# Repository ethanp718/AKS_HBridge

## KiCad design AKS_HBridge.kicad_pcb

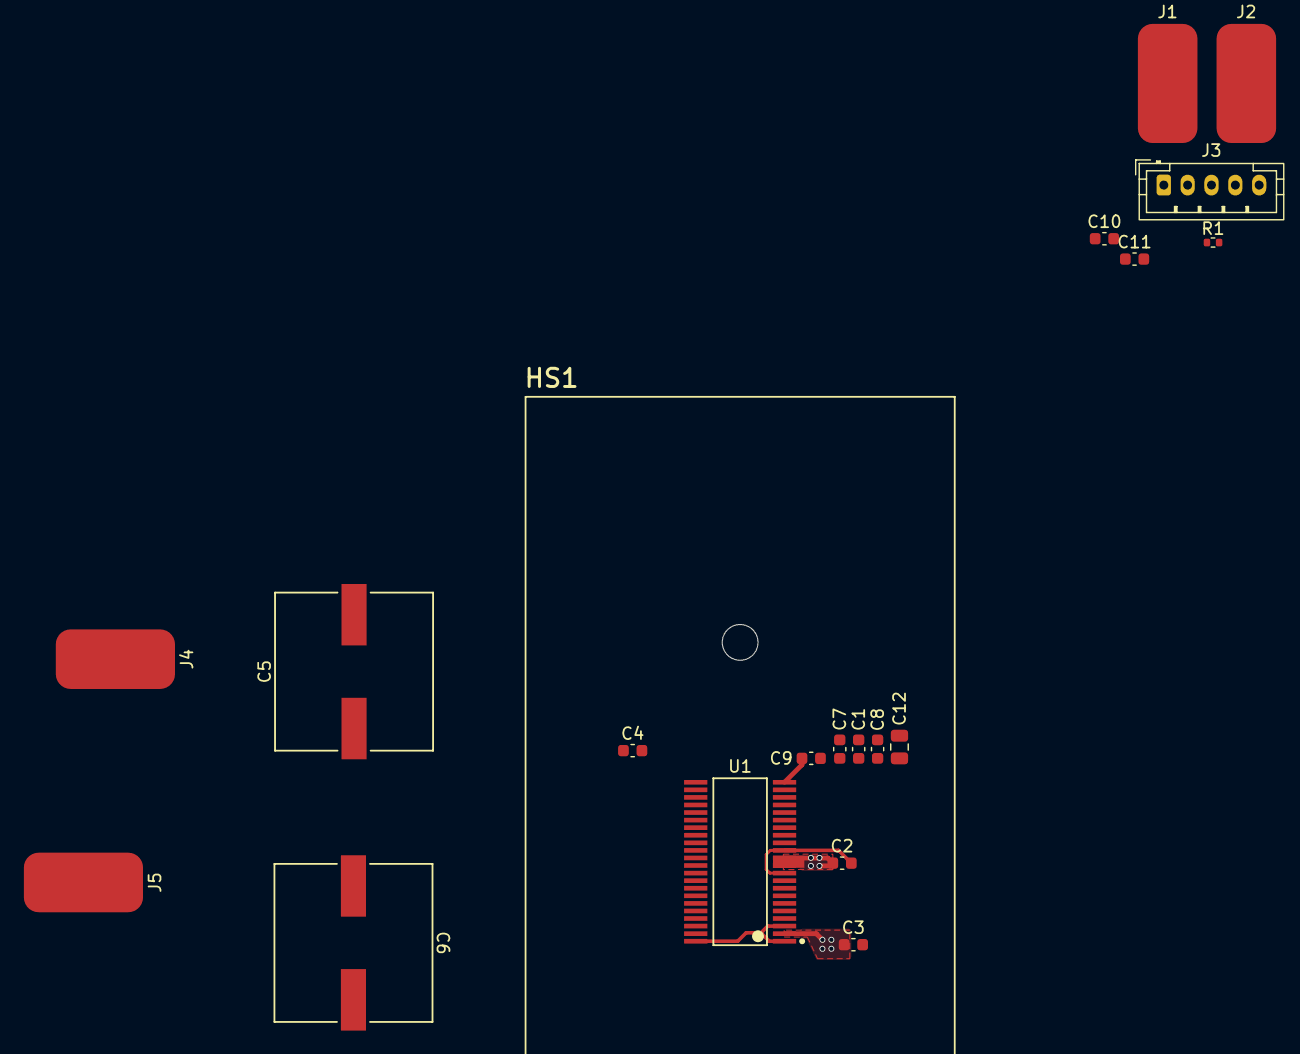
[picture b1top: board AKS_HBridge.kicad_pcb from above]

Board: 4 copper layers, 20 parts (0 on the bottom side), 12 nets.

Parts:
C1, C2, C3: 10nF; C_0603_1608Metric
C4, C8, C11: 100nF; C_0603_1608Metric
C5, C6: 100uF; CHEMI-KE0
C7: 1nF; C_0603_1608Metric
C9, C10: 1uF; C_0603_1608Metric
C12: 1uF; C_0805_2012Metric
HS1: Heatsink_Pad; FP-ATS-TI10P-519-C1-R3_HEAT_SINK-MFG
J1: MOTA; SolderWirePad_1x01_SMD_5x10mm
J2: MOTB; SolderWirePad_1x01_SMD_5x10mm
J3: Control; JST_PH_B5B-PH-K_1x05_P2.00mm_Vertical
J4: BATT+; SolderWirePad_1x01_SMD_5x10mm
J5: BATT-; SolderWirePad_1x01_SMD_5x10mm
R1: 10k; R_0402_1005Metric
U1: DRV8262DDVR; DDV0044E-IPC_A

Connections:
/FAULT_N: J3.4, R1.2, U1.41 (FAULT_N)
/IN1: J3.1, U1.26 (IN1)
/IN2: J3.2, U1.27 (IN2)
/MOTA: J1.1 (Pin_1_1), U1.4 (OUT3), U1.5 (OUT3), U1.6 (OUT3), U1.17 (OUT1), U1.18 (OUT1), U1.19 (OUT1)
/MOTB: J2.1 (Pin_1_1), U1.7 (OUT4), U1.8 (OUT4), U1.9 (OUT4), U1.14 (OUT2), U1.15 (OUT2), U1.16 (OUT2)
/SLEEP_N: J3.3, U1.25 (SLEEP_N)
GND: C1.2, C2.2, C3.2, C5.2, C6.2, C7.2, C8.2, C10.2, C11.2, C12.2, J3.5, J5.1 (Pin_1_1), U1.1 (GND), U1.3 (PGND34), U1.10 (PGND34), U1.13 (PGND12), U1.20 (PGND12), U1.30 (DECAY), U1.32 (TOFF), U1.36 (IPROPI1_IPROPI), U1.37 (IPROPI2_IPROPI), U1.44 (GND)
unnamed: C4.1, U1.23 (CPH)
unnamed: C4.2, U1.24 (CPL)
unnamed: C9.2, U1.22 (VCP)
VBUS: C1.1, C2.1, C3.1, C5.1, C6.1, C7.1, C8.1, C9.1, C12.1, J4.1 (Pin_1_1), U1.2 (VM), U1.11 (VM), U1.12 (VM), U1.21 (VM)
VCC: C10.1, C11.1, R1.1, U1.33 (VREF1_VREF), U1.34 (VREF2_VREF), U1.38 (MODE2), U1.39 (MODE1), U1.40 (OCPM), U1.42 (VCC), U1.43 (DVDD)
